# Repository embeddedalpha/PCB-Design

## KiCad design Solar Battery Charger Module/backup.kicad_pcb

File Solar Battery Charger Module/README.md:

<h1> Solar Battery Charger Module </h1>

<h4> 1: Black</h4>

<h4> 2: Green </h4>

<h4> 3: </h4>

<h4> 4: </h4>

<h4> 5: </h4>

<h4> 6: </h4>

<h4> 7: </h4>

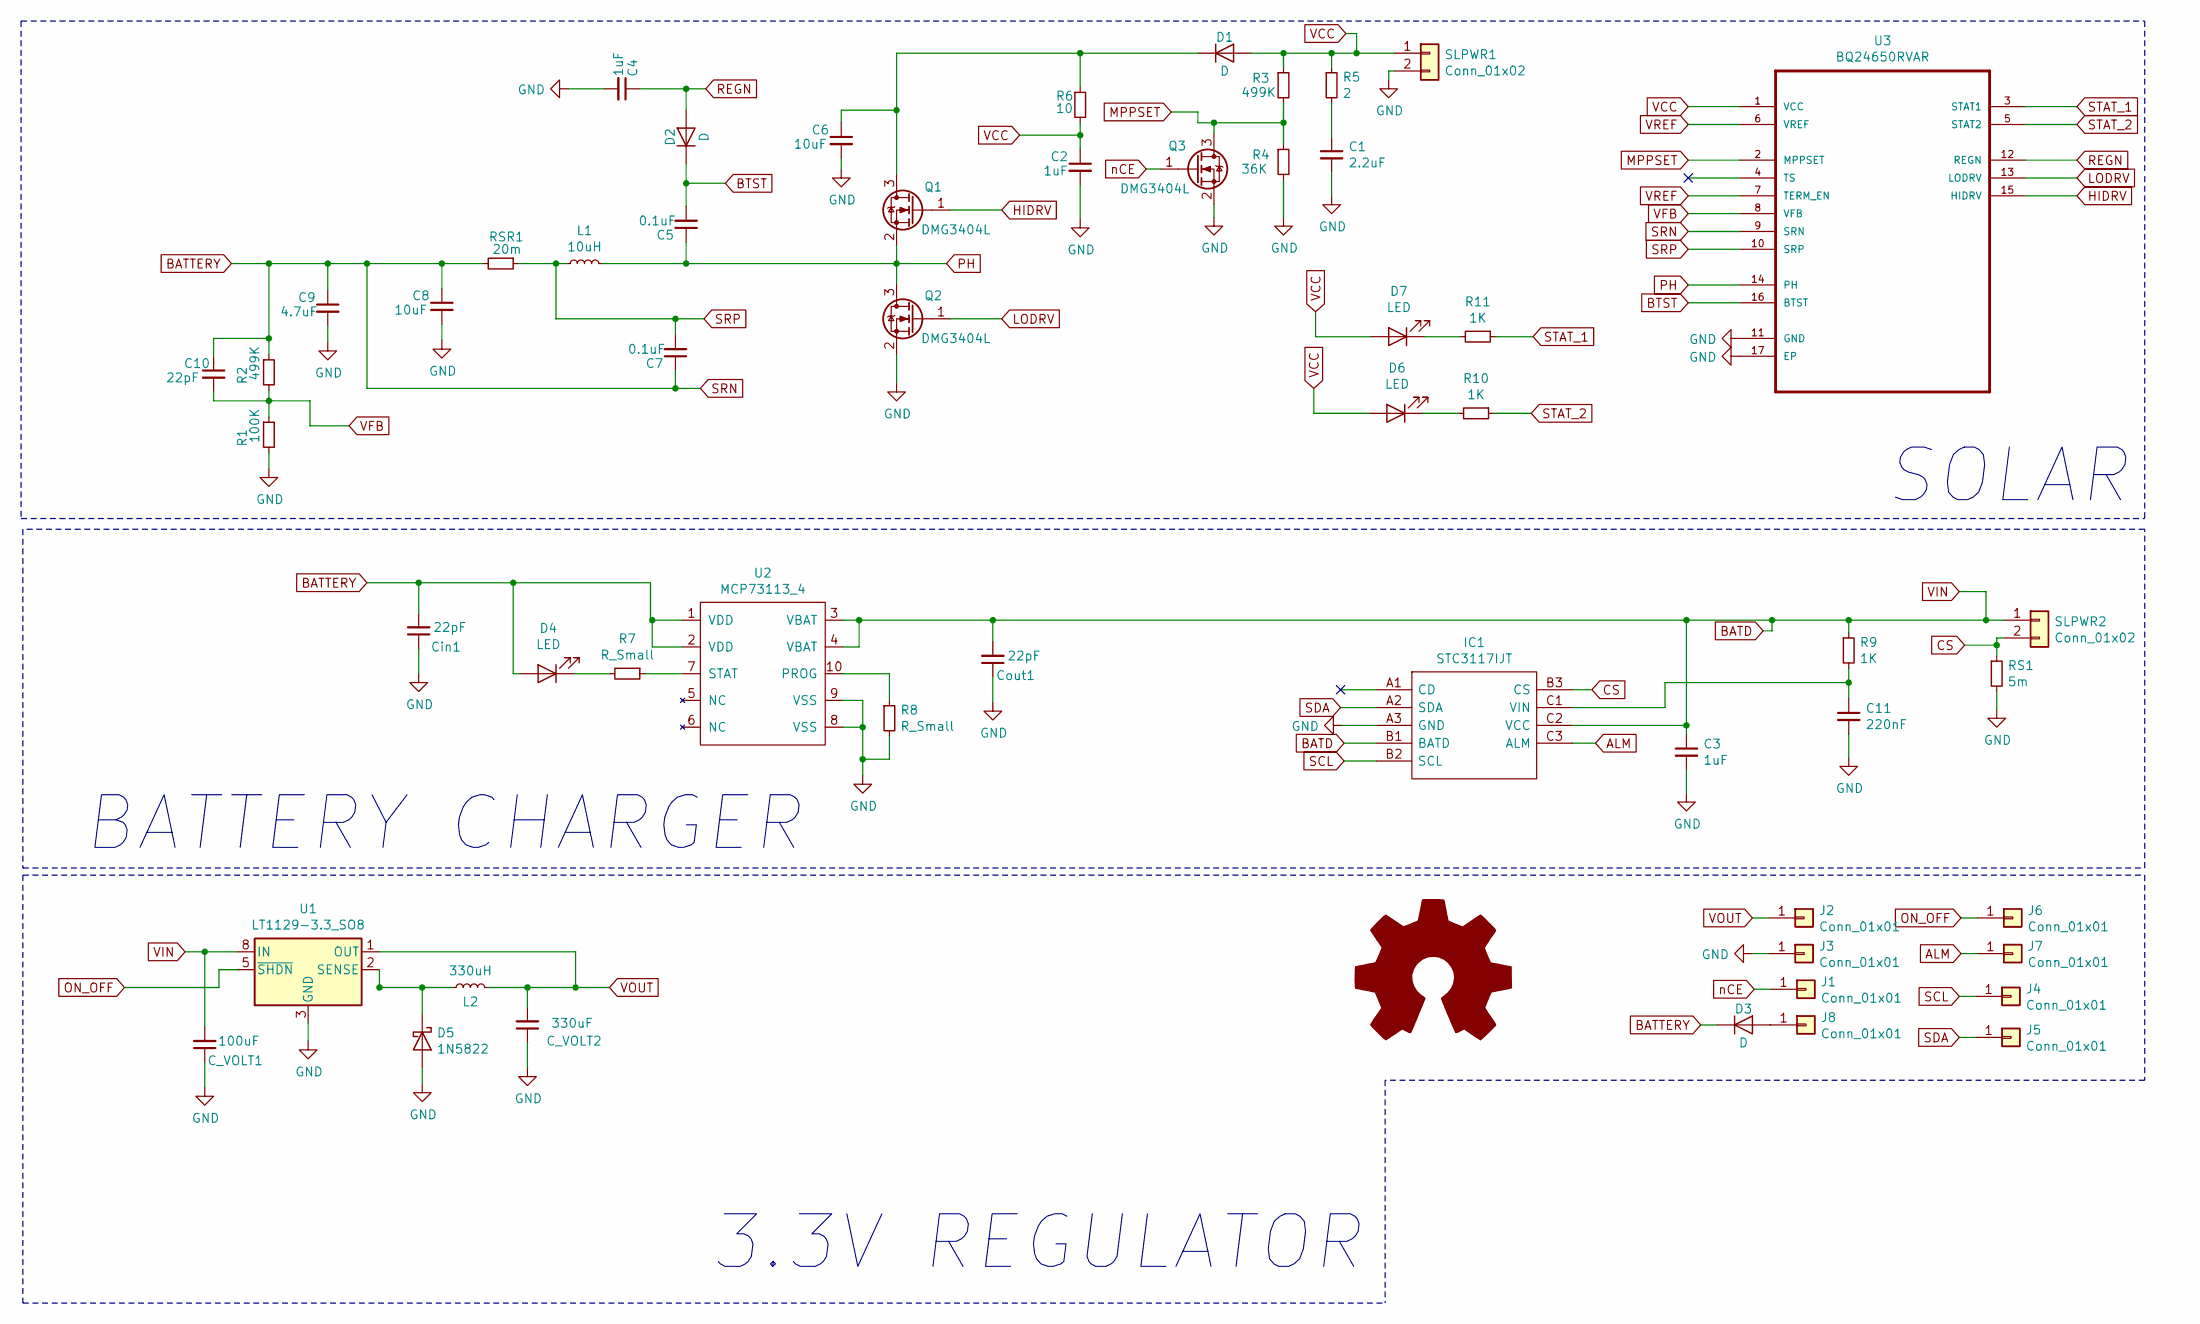
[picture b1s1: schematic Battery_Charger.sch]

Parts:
C1: 2.2uF; C_0201_0603Metric
C2, C3, C4: 1uF; C_0201_0603Metric
C5, C7: 0.1uF; C_0201_0603Metric
C6, C8: 10uF; C_0201_0603Metric
C9: 4.7uF; C_0201_0603Metric
C10: 22pF; C_0201_0603Metric
C11: 220nF; C_0201_0603Metric
C_VOLT1: 100uF; C_0201_0603Metric
C_VOLT2: 330uF; C_0201_0603Metric
Cin1: 22pF; C_0201_0603Metric
Cout1: 22pF; C_0201_0603Metric
D1, D2, D3: D; D_0201_0603Metric
D4, D6, D7: LED; LED_0201_0603Metric
D5: 1N5822; D_0201_0603Metric
IC1: STC3117IJT; BGA9C40P3X3_146X156X66; Mouser Part Number 511-STC3117IJT
J1, J2, J3, J4, J5, J6, J7, J8: Conn_01x01; Module_Footprint
L1: 10uH; L_0201_0603Metric
L2: 330uH; L_0201_0603Metric
Q1, Q2, Q3: DMG3404L; SOT-23
R1: 100K; R_0201_0603Metric
R2, R3: 499K; R_0201_0603Metric
R4: 36K; R_0201_0603Metric
R5: 2; R_0201_0603Metric
R6: 10; R_0201_0603Metric
R7, R8: R_Small; R_0201_0603Metric
R9, R10, R11: 1K; R_0201_0603Metric
RS1: 5m; R_0201_0603Metric
RSR1: 20m; R_0201_0603Metric
SLPWR1, SLPWR2: Conn_01x02; JST_PH_B2B-PH-SM4-TB_1x02-1MP_P2.00mm_Vertical
U1: LT1129-3.3_SO8; SOIC-8_3.9x4.9mm_P1.27mm
U2: MCP73113_4; MCP73113
U3: BQ24650RVAR; QFN50P350X350X100-17N

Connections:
ALM: IC1.C3 (ALM), J7.1
BATD: C3.1, C_VOLT1.2, Cout1.2, IC1.B1 (BATD), IC1.C2 (VCC), R9.1, SLPWR2.1, U1.8 (IN), U2.3 (VBAT), U2.4 (VBAT)
BATTERY: C7.1, C8.1, C9.1, C10.1, Cin1.2, D3.1 (K), D4.2 (A), R2.1, RSR1.2, U2.1 (VDD), U2.2 (VDD), U3.9 (SRN)
BTST: C5.2, D2.1 (K), U3.16 (BTST)
CS: IC1.B3 (CS), RS1.1, SLPWR2.2
GND: C1.2, C2.2, C3.2, C4.2, C6.2, C8.2, C9.2, C11.2, C_VOLT1.1, C_VOLT2.1, Cin1.1, Cout1.1, D5.2 (A), IC1.A3 (GND), J3.1, Q2.2 (S), Q3.2 (S), R1.2, R4.2, R8.2, RS1.2, SLPWR1.2, U1.3 (GND), U1.6 (GND), U1.7 (GND), U2.8 (VSS), U2.9 (VSS), U3.11 (GND), U3.17 (EP)
HIDRV: Q1.1 (G), U3.15 (HIDRV)
LODRV: Q2.1 (G), U3.13 (LODRV)
MPPSET: Q3.3 (D), R3.2, R4.1, U3.2 (MPPSET)
unnamed: C1.1, R5.2
unnamed: C6.1, D1.1 (K), Q1.3 (D), R6.1
unnamed: C11.1, IC1.C1 (VIN), R9.2
unnamed: D3.2 (A), J8.1
unnamed: D4.1 (K), R7.2
unnamed: D5.1 (K), L2.1, U1.2 (SENSE), U1.4 (NC)
unnamed: D6.1 (K), R10.2
unnamed: D7.1 (K), R11.2
unnamed: R7.1, U2.7 (STAT)
unnamed: R8.1, U2.10 (PROG)
ON_OFF: J6.1, U1.5 (~SHDN)
PH: C5.1, L1.2, Q1.2 (S), Q2.3 (D), U3.14 (PH)
REGN: C4.1, D2.2 (A), U3.12 (REGN)
SCL: IC1.B2 (SCL), J4.1
SDA: IC1.A2 (SDA), J5.1
SRP: C7.2, L1.1, RSR1.1, U3.10 (SRP)
STAT_1: R11.1, U3.3 (STAT1)
STAT_2: R10.1, U3.5 (STAT2)
VCC: C2.1, D1.2 (A), D6.2 (A), D7.2 (A), R3.1, R5.1, R6.2, SLPWR1.1, U3.1 (VCC)
VFB: C10.2, R1.1, R2.2, U3.8 (VFB)
VOUT: C_VOLT2.2, J2.1, L2.2, U1.1 (OUT)
VREF: U3.6 (VREF), U3.7 (TERM_EN)
nCE: J1.1, Q3.1 (G)

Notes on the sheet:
SOLAR
BATTERY CHARGER
3.3V REGULATOR

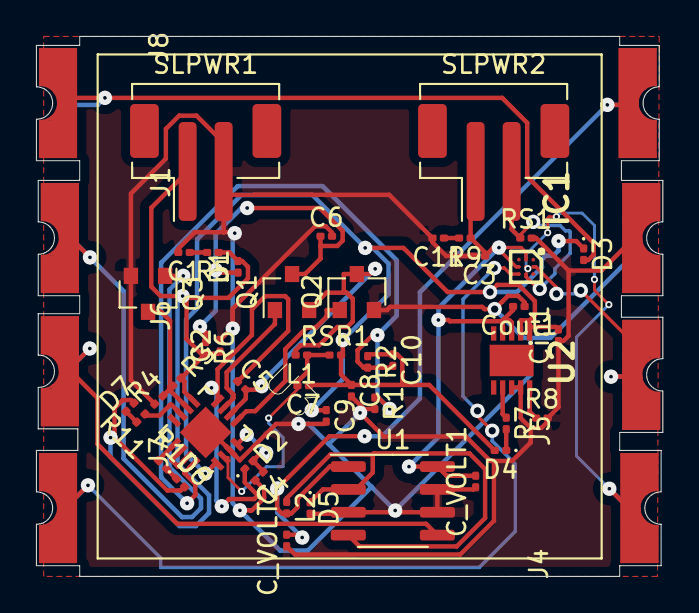
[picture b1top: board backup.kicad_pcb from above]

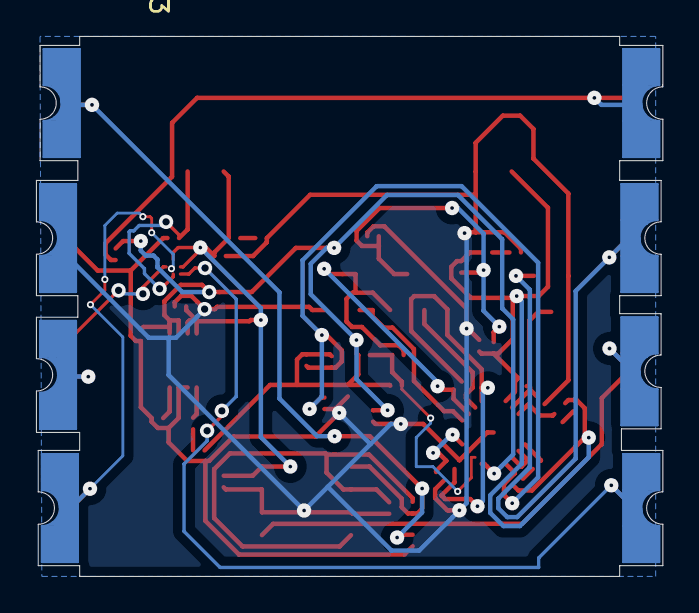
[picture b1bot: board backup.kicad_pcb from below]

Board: 2 copper layers, 34.8 x 30.0 mm, 54 parts (2 on the bottom side), 32 nets.

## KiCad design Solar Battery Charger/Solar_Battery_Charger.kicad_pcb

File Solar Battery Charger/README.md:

<h1> Solar Battery Charger Module </h1>

<h4> 1: </h4>

<h4> 2: </h4>

<h4> 3: Copper</h4>

<h4> 4: Front Copper</h4>

<h4> 5: Back Copper</h4>

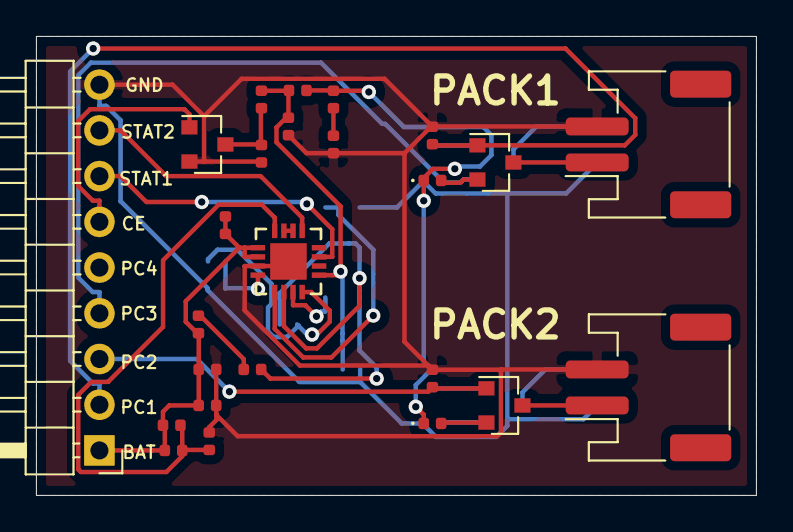
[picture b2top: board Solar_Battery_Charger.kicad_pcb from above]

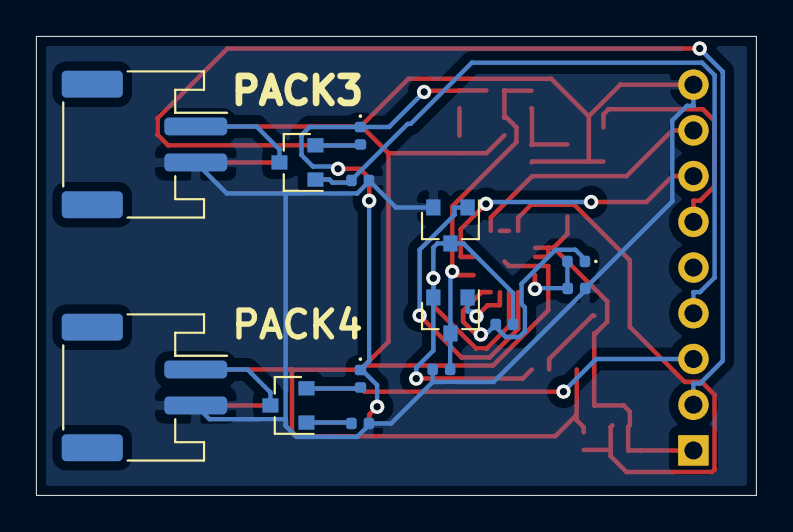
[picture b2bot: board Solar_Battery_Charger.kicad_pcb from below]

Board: 2 copper layers, 40.0 x 25.5 mm, 39 parts (14 on the bottom side), 29 nets.

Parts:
C1: 2.2U; C_0402_1005Metric
C2, C4: 1U; C_0402_1005Metric
C5, C7: 0.1U; C_0402_1005Metric
C6, C8: 10U; C_0402_1005Metric
C9: 4.7U; C_0402_1005Metric
C10: 22P; C_0402_1005Metric
D1, D2, D3, D4: D; D_0402_1005Metric
D5: D_Schottky; D_0402_1005Metric
J1, J2, J3, J4: Conn_01x02; JST_PH_S2B-PH-SM4-TB_1x02-1MP_P2.00mm_Horizontal
J5: Conn_01x09; PinHeader_1x09_P2.54mm_Horizontal
L1: 10U; L_0402_1005Metric
Q1, Q2, Q3, Q4, Q5, Q6, Q7: 2N7002; SOT-23
R1: 100K; R_0402_1005Metric
R2, R3: 499K; R_0402_1005Metric
R4: 36K; R_0402_1005Metric
R5: 2; R_0402_1005Metric
R6: 10; R_0402_1005Metric
RMOS1, RMOS2, RMOS3, RMOS4: 10K; R_0402_1005Metric
RSR1: 20m; R_0402_1005Metric
U1: BQ24650RVAR; QFN50P350X350X100-17N

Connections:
BATTERY_PACK: C7.1, C7.2, C8.1, C9.1, C10.1, J5.1, R2.1, RSR1.2, U1.9, U1.10
BTST: C5.2, D5.1, U1.16
CE: J5.6, Q3.1
GND: C1.2, C2.2, C4.1, C6.2, C8.2, C9.2, J1.2, J2.2, J3.2, J4.2, J5.9, Q2.2, Q3.2, R1.2, R4.1, RMOS1.2, RMOS2.2, RMOS3.2, RMOS4.2, U1.11, U1.17
unnamed: C1.1, R5.1
unnamed: D1.1, D2.1, D3.1, D4.1, R5.2, R6.2
unnamed: D1.2, Q4.2
unnamed: D2.2, Q5.2
unnamed: D3.2, Q6.2
unnamed: D4.2, Q7.2
unnamed: J1.1, Q4.3
unnamed: J2.1, Q5.3
unnamed: J3.1, Q6.3
unnamed: J4.1, Q7.3
unnamed: L1.2, RSR1.1
unnamed: Q1.1, U1.15
unnamed: Q2.1, U1.13
unnamed: Q3.3, R3.1, R4.2, U1.2
unnamed: U1.6, U1.7
PACK1_CONTROL: J5.2, Q4.1, RMOS1.1
PACK2_CONTROL: J5.3, Q5.1, RMOS2.1
PACK3_CONTROL: J5.4, Q6.1, RMOS3.1
PACK4_CONTORL: Q7.1, RMOS4.1
PH: C5.1, L1.1, Q1.2, Q2.3, U1.14
REGN: C4.2, D5.2, U1.12
STAT1: J5.7, U1.3
STAT2: J5.8, U1.5
VCC_PACK: C2.1, C6.1, Q1.3, R3.2, R6.1, U1.1
VFB: C10.2, R1.1, R2.2, U1.8

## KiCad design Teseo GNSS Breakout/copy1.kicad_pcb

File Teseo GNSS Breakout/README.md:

<H1> Teseo LIV3R GNSS Breakout </H1>

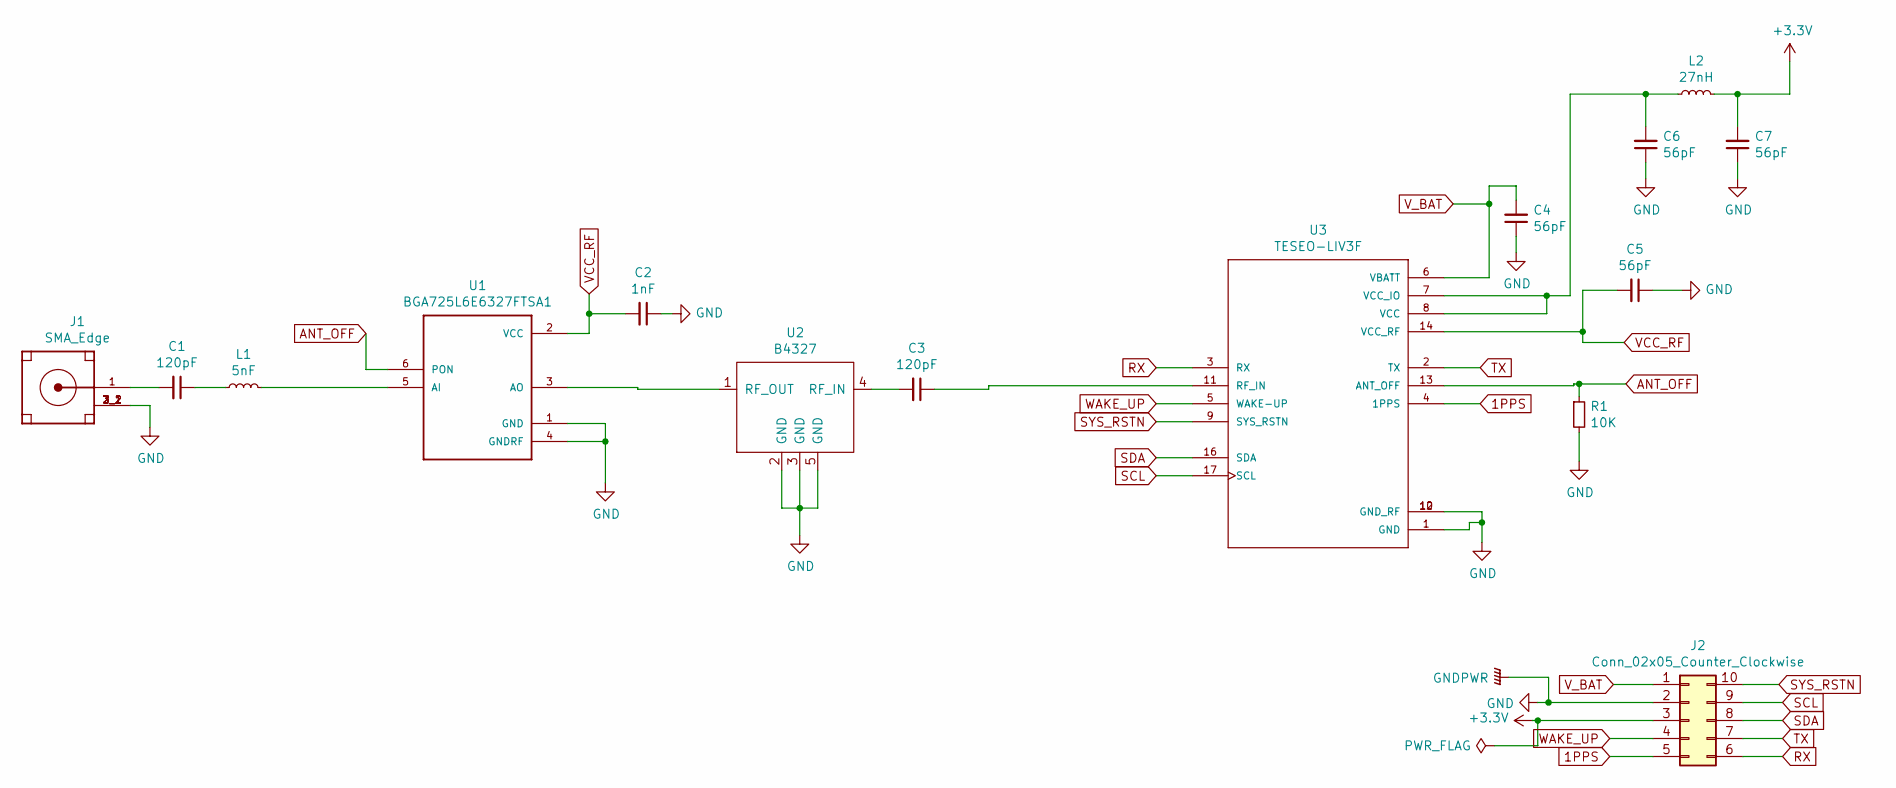
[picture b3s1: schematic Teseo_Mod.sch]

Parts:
C1, C3: 120pF; C_0201_0603Metric
C2: 1nF; C_0201_0603Metric
C4, C5, C6, C7: 56pF; C_0201_0603Metric
J1: SMA_Edge; SMA-J-P-H-ST-EM1
J2: Conn_02x05_Counter_Clockwise; PinHeader_2x05_P2.54mm_Horizontal
L1: 5nF; L_0201_0603Metric
L2: 27nH; L_0201_0603Metric
R1: 10K; L_0201_0603Metric
U1: BGA725L6E6327FTSA1
U2: B4327
U3: TESEO-LIV3F

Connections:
1PPS: J2.5, U3.4 (1PPS)
+3V3: C7.2, J2.3, L2.2
ANT_OFF: R1.1, U1.6 (PON), U3.13 (ANT_OFF)
GND: C2.1, C4.1, C5.1, C6.1, C7.1, J1.2_1 (GND), J1.2_2 (GND), J1.3_1 (GND), J1.3_2 (GND), J2.2, R1.2, U1.1 (GND), U1.4 (GNDRF), U2.2 (GND), U2.3 (GND), U2.5 (GND), U3.1 (GND), U3.10 (GND_RF), U3.12 (GND_RF)
unnamed: C1.1, L1.1
unnamed: C1.2, J1.1 (SIGNAL)
unnamed: C3.1, U3.11 (RF_IN)
unnamed: C3.2, U2.4 (RF_IN)
unnamed: C6.2, L2.1, U3.7 (VCC_IO), U3.8 (VCC)
unnamed: L1.2, U1.5 (AI)
unnamed: U1.3 (AO), U2.1 (RF_OUT)
RX: J2.6, U3.3 (RX)
SCL: J2.9, U3.17 (SCL)
SDA: J2.8, U3.16 (SDA)
SYS_RSTN: J2.10, U3.9 (SYS_RSTN)
TX: J2.7, U3.2 (TX)
VCC_RF: C2.2, C5.2, U1.2 (VCC), U3.14 (VCC_RF)
V_BAT: C4.2, J2.1, U3.6 (VBATT)
WAKE_UP: J2.4, U3.5 (WAKE-UP)

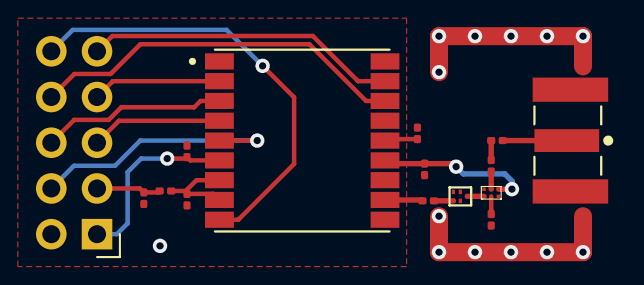
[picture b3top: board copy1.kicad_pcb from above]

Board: 4 copper layers, 15 parts (0 on the bottom side), 19 nets.
